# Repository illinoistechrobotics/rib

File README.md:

# Illinois Tech Robotics - Robot Interface Board (RIB)

This is a PCB design based around the existing Goliath protoboards, but adapted to work with a Raspberry Pi Pico (W), but is also usable with other robot designs using solder bridge jumpers to support various configurations. 

# Features

## Output
The majority of the circuitry allows connecting 2 OSMC's (Open Source Motor Controller) v3.22 over RJ45. They are wired with pin 2 through 9, as CAT6 only has 8 conductors and pin 1 and 10 are the same as 2 and 9 respectively, in this case we don't need the increased current offered by the extra pins.

The 10 connections for the OSMCs are just PWM or digital outputs using MCT9001 Optocouplers, by default set up for 12V (Or whatever is supplied to VIN), but with a jumper it can be set to 5V or 3.3V logic to interface with a variety of motor controllers.

There is a MAX6959 36-channel LED driver chip, that independently controls the 2-digit 7-segment display, the status LEDs of the ethernet ports, and the 3 RGB LEDs present.

## Input
2 rotary quadrature encoders can be connected with RJ45, intended to be used with the Pico's PIO. The RJ45 connections for the encoders have breakouts for Z inputs (for absolute positioning) or 2 more encoders with relative positioning only. These inputs are not connected to the Pico by default due to the limited number of GPIO pins.

There is a MCP3008 ADC which is used for battery voltage & current monitoring.

## I/O

There are 2 PCF8574 I/O expanders which are mostly ununsed, allowing for the connection of low bandwith devices (e.g. enable pins, end stops / limit switches, basic on/off logic) as their speed is limited by the I2C bus. That said, the interrupt pins are broken out and can be optionally used for a decent connection for a rotary encoder.

The first I/O expander is connected to 2 N-channel MOSFETs that are connected to the board's input voltage for VIN @ 2A (total) controllable high-power output.

There are 3 extra GPIO pins exposed, which can be used for connecting e.g. the extra encoder pins, the I/O expander interrupts, or I2C communication to other RIB(s) in order to create a megaRIB for connecting more than 2 OSMCs.

Finally, there is a place for a Digi xBee to sit and communicate with the robot over 2.4Ghz / 900 MHz radio.

## POWER 

Additionally, the PCB pulls power in from the OSMCs over the RJ45 connections or the top left terminal block. The RIB can take in from 8 to 60V of power, or you can provide 5V via headers directly. If it's necessary, the RIB can be powered by a 2S Lithium battery, the power supply can still function at around 7V in.

The onboard 5V switching power supply can provide ~1.8A and the 3v3 regulator, which pulls from the 5V line, can use up to the same 1.8A limit. The 3v3 regulator exists to  provide extra power to the xBee and 3v3 logic without having to put strain on the Pico.

The power inputs on the OSMC RJ45's can also be changed to *output* power and will match the logic voltage 5V/3.3V.

# Programming

The Pi Pico W can be programming with [Arduino-Pico](https://arduino-pico.readthedocs.io/en/latest/), the Pico C++ SDK, Micro/CircuitPython, or Embassy Rust framework. Code examples below are written based on the Arduino-Pico framework. *Note: we discovered a bug in Arduino-Pico's setXX functions affecting the RIB that is only fixed in v3.6.0 or higher.*

Things to know for programming the hardware on the RIB:

The xBee is connected to UART0 / Serial1 on the Pico via pins 16 & 17 for TX & RX respectively. 

	Serial1.setRX(17);
  	Serial1.setTX(16);

The I2C bus for the LED driver and I/O expanders is connected to I2C1 / Wire, pins 20 & 21 for SDA and SCL respectively. 

    Wire.setSDA(20);
    Wire.setSCL(21);

The LED driver has address 0x38. There is no library for the MAX6959 available online, we wrote one in [rib-test-code](https://git.myitr.org/adeck/rib-test-code). Look for lines like `Wire.beginTransmission(0x38)` and functions like `set_digit()` for example.

The I/O expanders have addresses 0x20 for the top one (connected to MOSFETs) and 0x21 for the bottom one.

The library `xreef/PCF8574` has the ability to set pins as well, so the code you would use is

    PCF8574 ioex1(0x20, 20, 21);
    PCF8574 ioex2(0x21, 20, 21);

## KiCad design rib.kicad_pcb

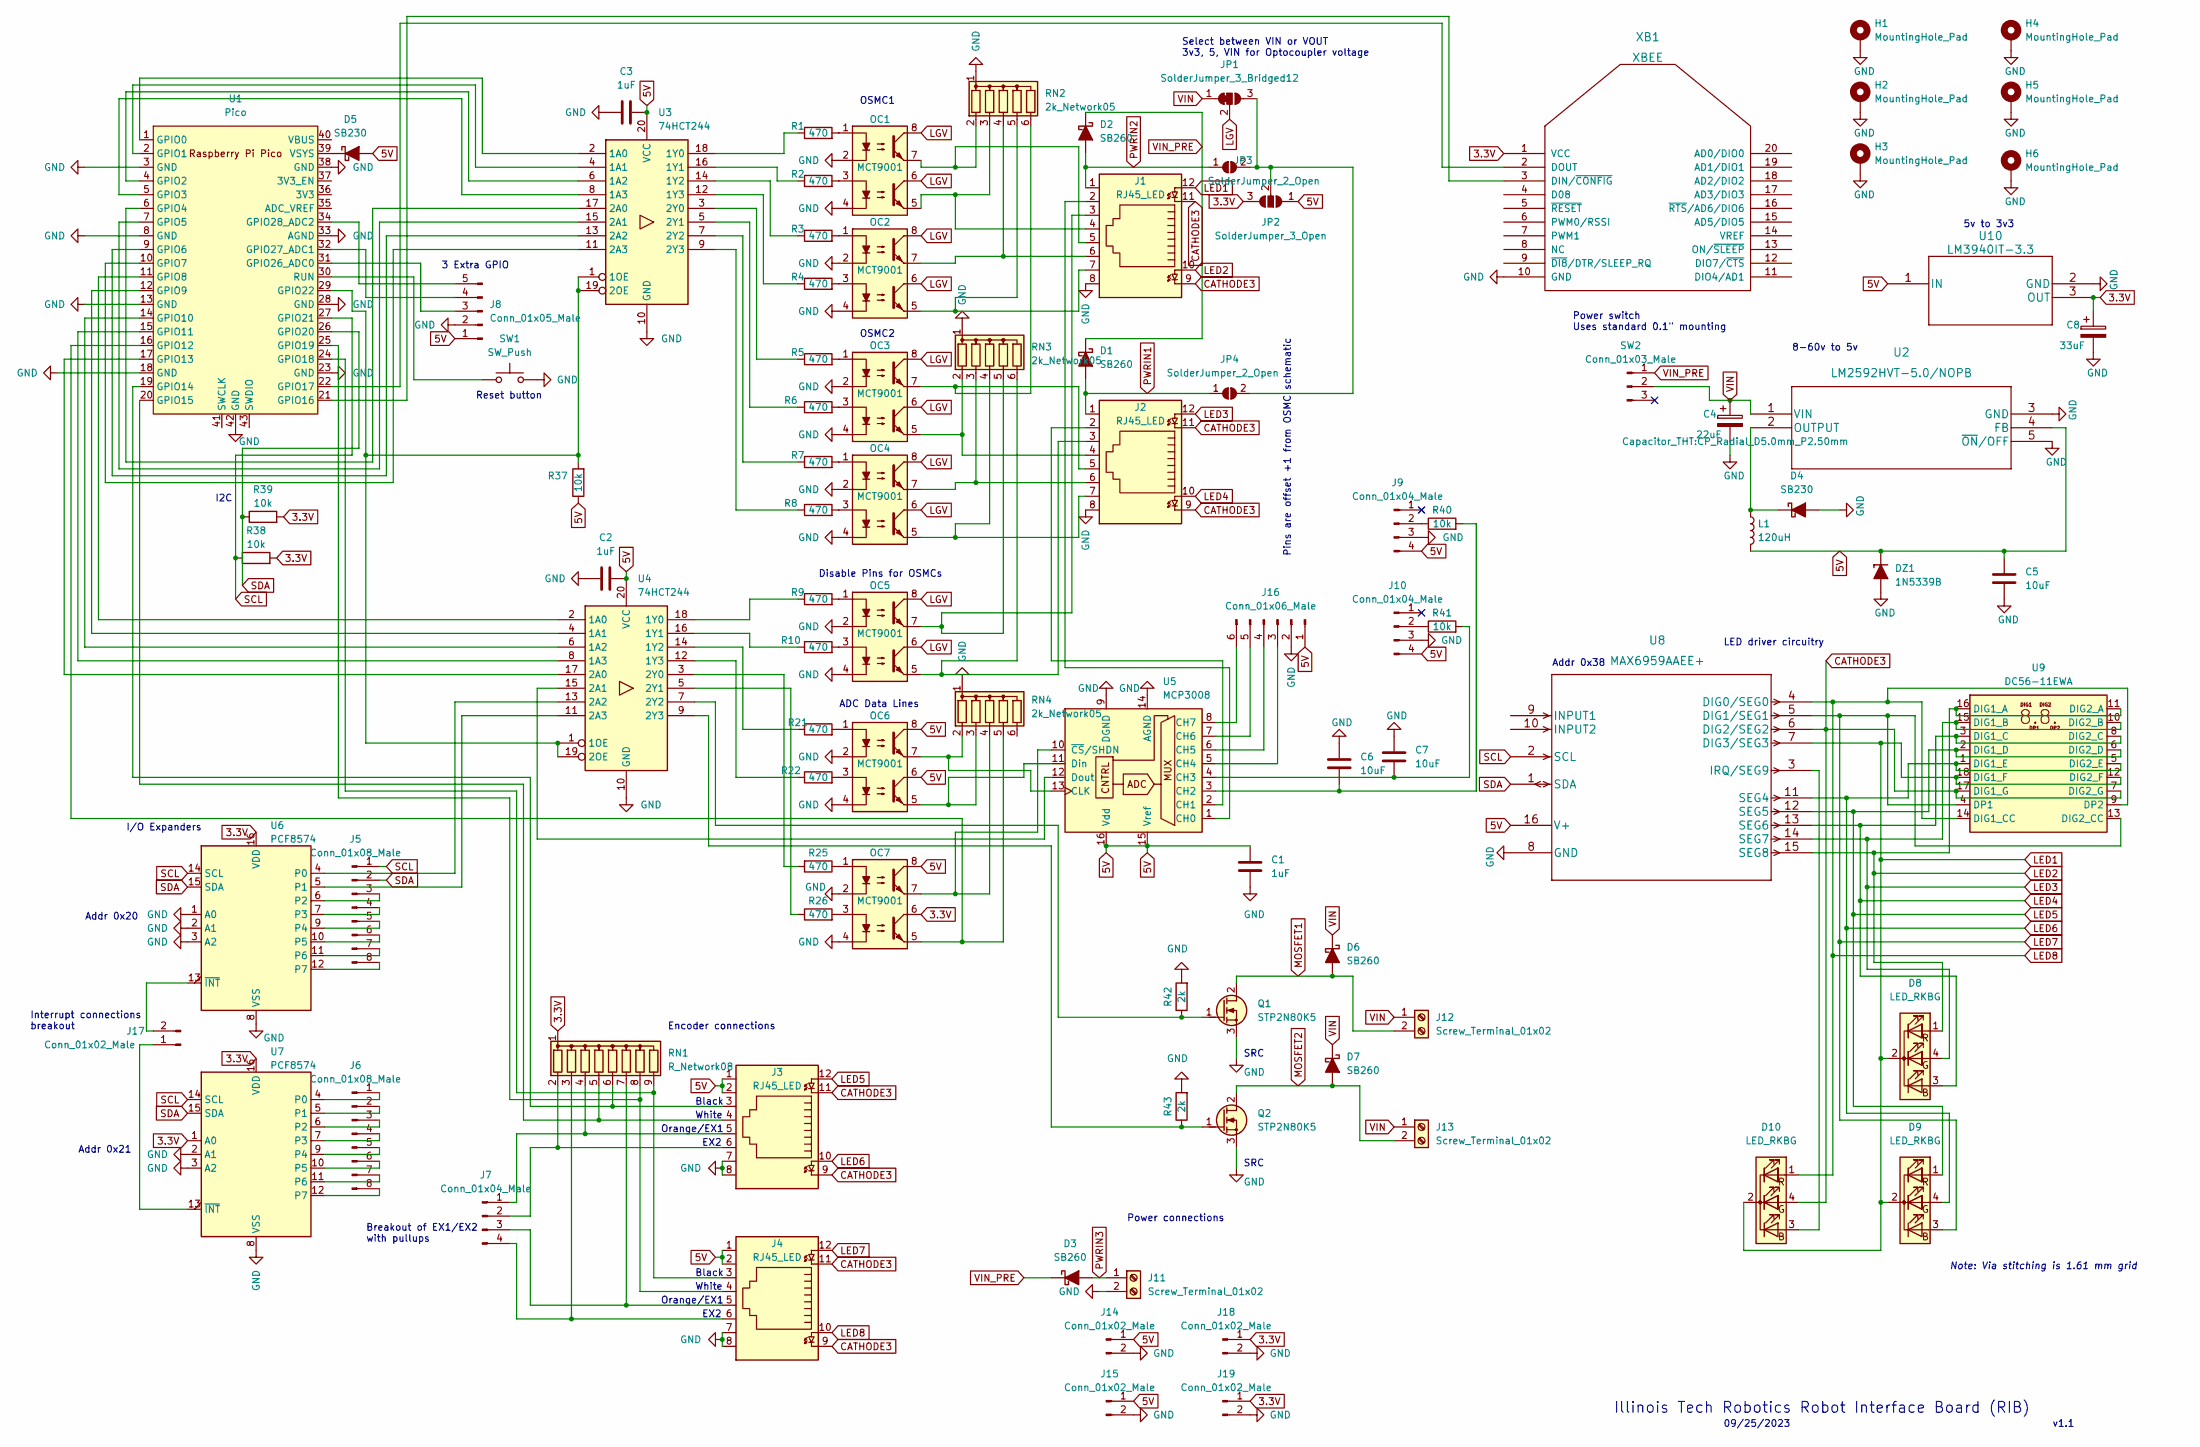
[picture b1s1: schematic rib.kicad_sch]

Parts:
C1, C2, C3: 1uF; C_Rect_L7.0mm_W4.5mm_P5.00mm
C4: 22uF; CP_Radial_D5.0mm_P2.50mm
C5, C6, C7: 10uF; C_Rect_L7.0mm_W4.5mm_P5.00mm
C8: 33uF; CP_Radial_D5.0mm_P2.50mm
D1, D2, D3, D6, D7: SB260; D_DO-15_P10.16mm_Horizontal
D4, D5: SB230; D_DO-15_P10.16mm_Horizontal
D8, D9, D10: LED_RKBG; LED_D5.0mm-4_RGB_Staggered_Pins
DZ1: 1N5339B; D_5W_CASE-017AA_P12.70mm_Horizontal_Zener
H1, H2, H3, H4, H5, H6: MountingHole_Pad; MountingHole_4.3mm_M4_Pad_Via
J1, J2, J3, J4: RJ45_LED; RJ45_Amphenol_RJHSE538X
J5, J6: Conn_01x08_Male; PinHeader_1x08_P2.54mm_Vertical
J7, J9, J10: Conn_01x04_Male; PinHeader_1x04_P2.54mm_Vertical
J8: Conn_01x05_Male; PinHeader_1x05_P2.54mm_Vertical
J11, J12, J13: Screw_Terminal_01x02; TerminalBlock_Phoenix_MKDS-1,5-2_1x02_P5.00mm_Horizontal
J14, J15, J17, J18, J19: Conn_01x02_Male; PinHeader_1x02_P2.54mm_Vertical
J16: Conn_01x06_Male; PinHeader_1x06_P2.54mm_Vertical
JP1: SolderJumper_3_Bridged12; SolderJumper-3_P1.3mm_Open_Pad1.0x1.5mm
JP2: SolderJumper_3_Open; SolderJumper-3_P1.3mm_Open_Pad1.0x1.5mm
JP3, JP4: SolderJumper_2_Open; SolderJumper-2_P1.3mm_Open_Pad1.0x1.5mm
L1: 120uH; L_Radial_D12.5mm_P7.00mm_Fastron_09HCP
OC1, OC2, OC3, OC4, OC5, OC6, OC7: MCT9001; DIP-8_W7.62mm_Socket
Q1, Q2: STP2N80K5; TO-220-3_Vertical_GDS
R1, R2, R3, R4, R5, R6, R7, R8, R9, R10, R21, R22, R25, R26: 470; R_Axial_DIN0207_L6.3mm_D2.5mm_P10.16mm_Horizontal
R37, R38, R39, R40, R41: 10k; R_Axial_DIN0207_L6.3mm_D2.5mm_P10.16mm_Horizontal
R42, R43: 2k; R_Axial_DIN0207_L6.3mm_D2.5mm_P10.16mm_Horizontal
RN1: R_Network08; R_Array_SIP9
RN2, RN3, RN4: 2k_Network05; R_Array_SIP6
SW1: SW_Push; SW_Tactile_PUSH_4.5mm_H3.8mm_TS_C016
SW2: Conn_01x03_Male; PinSocket_1x03_P2.54mm_Vertical
U1: Pico; RPi_Pico_SMD_TH
U2: LM2592HVT-5.0/NOPB; LM2592HVT-5.0&slash_NOPB
U3, U4: 74HCT244; DIP-20_W7.62mm_Socket
U5: MCP3008; DIP-16_W7.62mm_Socket
U6, U7: PCF8574; DIP-16_W7.62mm_Socket
U8: MAX6959AAEE+; DIP-16_W7.62mm_Socket
U9: DC56-11EWA; DA56-11SURKWA
U10: LM3940IT-3.3; TO-220-3_Vertical
XB1: XBEE; XBEE_PRO_PTH

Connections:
3.3V: C8.1, J18.1, J19.1, JP2.3 (B), OC7.6, R38.2, R39.2, RN1.1 (common), U6.16 (VDD), U7.1 (A0), U7.16 (VDD), U10.3 (OUT), XB1.1 (VCC)
5V: C1.1, C2.2, C3.2, C5.1, D5.2 (A), DZ1.1 (K), J3.1, J3.2, J4.1, J4.2, J8.1, J9.4, J10.4, J14.1, J15.1, J16.1, JP2.1 (A), L1.2, OC6.6, OC6.8, OC7.8, R37.1, U2.4 (FB), U3.20 (VCC), U4.20 (VCC), U5.15 (Vref), U5.16 (Vdd), U8.16 (V+), U10.1 (IN)
CATHODE3: D10.4 (GA), J1.9, J1.11, J2.9, J2.11, J3.9, J3.11, J4.9, J4.11, U8.6 (DIG2/SEG2), U9.7 (DIG2_G), U9.17 (DIG1_G)
GND: C1.2, C2.1, C3.1, C4.2, C5.2, C6.1, C7.1, C8.2, D4.2 (A), DZ1.2 (A), H1.1, H2.1, H3.1, H4.1, H5.1, H6.1, J1.8, J2.8, J3.7, J3.8, J4.7, J4.8, J8.2, J9.3, J10.3, J11.2, J14.2, J15.2, J16.2, J18.2, J19.2, OC1.2, OC1.4, OC2.2, OC2.4, OC3.2, OC3.4, OC4.2, OC4.4, OC5.2, OC5.4, OC6.2, OC6.4, OC7.2, OC7.4, Q1.3 (S), Q2.3 (S), R42.2, R43.2, RN2.1 (common), RN3.1 (common), RN4.1 (common), SW1.2, U1.3 (GND), U1.8 (GND), U1.13 (GND), U1.18 (GND), U1.23 (GND), U1.28 (GND), U1.33 (AGND), U1.38 (GND), U1.42 (GND), U2.3 (GND), U2.5 (~ON/OFF), U3.10 (GND), U4.10 (GND), U5.9 (DGND), U5.14 (AGND), U6.1 (A0), U6.2 (A1), U6.3 (A2), U6.8 (VSS), U7.2 (A1), U7.3 (A2), U7.8 (VSS), U8.8 (GND), U10.2 (GND), XB1.10 (GND)
LED1: D8.2 (K), D9.2 (K), D10.2 (K), J1.12, U8.7 (DIG3/SEG3), U9.12 (DIG2_F), U9.18 (DIG1_F)
LED2: D8.1 (RA), J1.10, U8.15 (SEG8), U9.11 (DIG2_A), U9.16 (DIG1_A)
LED3: D8.4 (GA), J2.12, U8.14 (SEG7), U9.10 (DIG2_B), U9.15 (DIG1_B)
LED4: D8.3 (BA), J2.10, U8.13 (SEG6), U9.3 (DIG1_C), U9.8 (DIG2_C)
LED5: D9.1 (RA), J3.12, U8.12 (SEG5), U9.2 (DIG1_D), U9.6 (DIG2_D)
LED6: D9.4 (GA), J3.10, U8.11 (SEG4), U9.1 (DIG1_E), U9.5 (DIG2_E)
LED7: D9.3 (BA), J4.12, U8.5 (DIG1/SEG1), U9.4 (DP1), U9.13 (DIG2_CC)
LED8: D10.1 (RA), J4.10, U8.4 (DIG0/SEG0), U9.9 (DP2), U9.14 (DIG1_CC)
LGV: JP1.2 (C), OC1.6, OC1.8, OC2.6, OC2.8, OC3.6, OC3.8, OC4.6, OC4.8, OC5.6, OC5.8
MOSFET1: D6.2 (A), J12.2, Q1.2 (D)
MOSFET2: D7.2 (A), J13.2, Q2.2 (D)
unnamed: D4.1 (K), L1.1, U2.2 (OUTPUT)
unnamed: D5.1 (K), U1.39 (VSYS)
unnamed: D10.3 (BA), U8.3 (IRQ/SEG9)
unnamed: J5.3, U6.6 (P2)
unnamed: J5.4, U6.7 (P3)
unnamed: J5.5, U6.9 (P4)
unnamed: J5.6, U6.10 (P5)
unnamed: J5.7, U6.11 (P6)
unnamed: J5.8, U6.12 (P7)
unnamed: J6.1, U7.4 (P0)
unnamed: J6.2, U7.5 (P1)
unnamed: J6.3, U7.6 (P2)
unnamed: J6.4, U7.7 (P3)
unnamed: J6.5, U7.9 (P4)
unnamed: J6.6, U7.10 (P5)
unnamed: J6.7, U7.11 (P6)
unnamed: J6.8, U7.12 (P7)
unnamed: J3.5, J7.1, RN1.4 (R3)
unnamed: J3.6, J7.2, RN1.2 (R1)
unnamed: J4.5, J7.3, RN1.7 (R6)
unnamed: J4.6, J7.4, RN1.3 (R2)
unnamed: J8.3, U1.31 (GPIO26_ADC0)
unnamed: J8.4, U1.32 (GPIO27_ADC1)
unnamed: J8.5, U1.34 (GPIO28_ADC2)
unnamed: J9.2, R40.1
unnamed: J10.2, R41.1
unnamed: J16.3, U5.5 (CH4)
unnamed: J16.4, U5.6 (CH5)
unnamed: J16.5, U5.7 (CH6)
unnamed: J16.6, U5.8 (CH7)
unnamed: J17.1, U7.13 (~INT)
unnamed: J17.2, U6.13 (~INT)
unnamed: JP1.3 (B), JP2.2 (C), JP3.2 (B), JP4.2 (B)
unnamed: OC1.1, R1.2
unnamed: OC1.3, R2.2
unnamed: OC2.1, R3.2
unnamed: OC2.3, R4.2
unnamed: OC3.1, R5.2
unnamed: OC3.3, R6.2
unnamed: OC4.1, R7.2
unnamed: OC4.3, R8.2
unnamed: OC5.1, R9.2
unnamed: OC5.3, R10.2
unnamed: OC6.1, R21.2
unnamed: OC6.3, R22.2
unnamed: OC7.1, R25.1
unnamed: OC7.3, R26.2
unnamed: Q1.1 (G), R42.1, U4.7 (2Y2)
unnamed: Q2.1 (G), R43.1, U4.9 (2Y3)
unnamed: J3.4, RN1.5 (R4), U1.20 (GPIO15)
unnamed: J3.3, RN1.6 (R5), U1.19 (GPIO14)
unnamed: J4.4, RN1.8 (R7), U1.25 (GPIO19)
unnamed: J4.3, RN1.9 (R8), U1.24 (GPIO18)
unnamed: J1.5, OC1.7, RN2.2 (R1)
unnamed: J1.4, OC1.5, RN2.3 (R2)
unnamed: J1.6, OC2.7, RN2.4 (R3)
unnamed: J1.7, OC2.5, RN2.5 (R4)
unnamed: J2.5, OC3.7, RN2.6 (R5)
unnamed: J2.4, OC3.5, RN3.2 (R1)
unnamed: J2.6, OC4.7, RN3.3 (R2)
unnamed: J2.7, OC4.5, RN3.4 (R3)
unnamed: J1.3, OC5.7, RN3.5 (R4)
unnamed: J2.3, OC5.5, RN3.6 (R5)
unnamed: OC6.7, RN4.2 (R1), U5.13 (CLK)
unnamed: OC6.5, RN4.3 (R2), U5.11 (Din)
unnamed: OC7.7, RN4.4 (R3), U5.10 (~CS/SHDN)
unnamed: OC7.5, RN4.5 (R4), U1.16 (GPIO12)
unnamed: U1.1 (GPIO0), U3.2 (1A0)
unnamed: U1.2 (GPIO1), U3.4 (1A1)
unnamed: U1.4 (GPIO2), U3.6 (1A2)
unnamed: U1.5 (GPIO3), U3.8 (1A3)
unnamed: U1.6 (GPIO4), U3.17 (2A0)
unnamed: U1.7 (GPIO5), U3.15 (2A1)
unnamed: U1.9 (GPIO6), U3.13 (2A2)
unnamed: U1.10 (GPIO7), U3.11 (2A3)
unnamed: U1.11 (GPIO8), U4.2 (1A0)
unnamed: U1.12 (GPIO9), U4.4 (1A1)
unnamed: U1.14 (GPIO10), U4.6 (1A2)
unnamed: U1.15 (GPIO11), U4.8 (1A3)
unnamed: U1.17 (GPIO13), U4.17 (2A0)
unnamed: U1.21 (GPIO16), XB1.3 (DIN/~CONFIG)
unnamed: U1.22 (GPIO17), XB1.2 (DOUT)
unnamed: R37.2, U1.29 (GPIO22), U3.1 (1OE), U3.19 (2OE), U4.1 (1OE), U4.19 (2OE)
unnamed: SW1.1, U1.30 (RUN)
unnamed: R1.1, U3.18 (1Y0)
unnamed: R2.1, U3.16 (1Y1)
unnamed: R3.1, U3.14 (1Y2)
unnamed: R4.1, U3.12 (1Y3)
unnamed: R5.1, U3.3 (2Y0)
unnamed: R6.1, U3.5 (2Y1)
unnamed: R7.1, U3.7 (2Y2)
unnamed: R8.1, U3.9 (2Y3)
unnamed: R9.1, U4.18 (1Y0)
unnamed: R10.1, U4.16 (1Y1)
unnamed: R21.1, U4.14 (1Y2)
unnamed: R22.1, U4.12 (1Y3)
unnamed: U4.15 (2A1), U5.12 (Dout)
unnamed: U4.13 (2A2), U6.4 (P0)
unnamed: U4.11 (2A3), U6.5 (P1)
unnamed: R25.2, U4.3 (2Y0)
unnamed: R26.1, U4.5 (2Y1)
unnamed: J1.2, U5.1 (CH0)
unnamed: J2.2, U5.2 (CH1)
unnamed: C6.2, R40.2, U5.3 (CH2)
unnamed: C7.2, R41.2, U5.4 (CH3)
PWRIN1: D1.2 (A), J2.1, JP4.1 (A)
PWRIN2: D2.2 (A), J1.1, JP3.1 (A)
PWRIN3: D3.2 (A), J11.1
SCL: J5.1, R38.1, U1.27 (GPIO21), U6.14 (SCL), U7.14 (SCL), U8.2 (SCL)
SDA: J5.2, R39.1, U1.26 (GPIO20), U6.15 (SDA), U7.15 (SDA), U8.1 (SDA)
VIN: C4.1, D6.1 (K), D7.1 (K), J12.1, J13.1, JP1.1 (A), SW2.2, U2.1 (VIN)
VIN_PRE: D1.1 (K), D2.1 (K), D3.1 (K), SW2.1

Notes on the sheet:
Reset button
Encoder connections
Black
I/O Expanders
Interrupt connections breakout
Power connections
5v to 3v3
3 Extra GPIO
Disable Pins for OSMCs
White
Illinois Tech Robotics Robot Interface Board (RIB)
OSMC2
OSMC1
ADC Data Lines
8-60v to 5v
Select between VIN or VOUT 3v3, 5, VIN for Optocoupler voltage
LED driver circuitry
SRC
Orange/EX1
Breakout of EX1/EX2 with pullups
09/25/2023
EX2
Note: Via stitching is 1.61 mm grid
Pins are offset +1 from OSMC schematic
Addr 0x20
Addr 0x38
I2C
Power switch Uses standard 0.1" mounting
v1.1
Addr 0x21

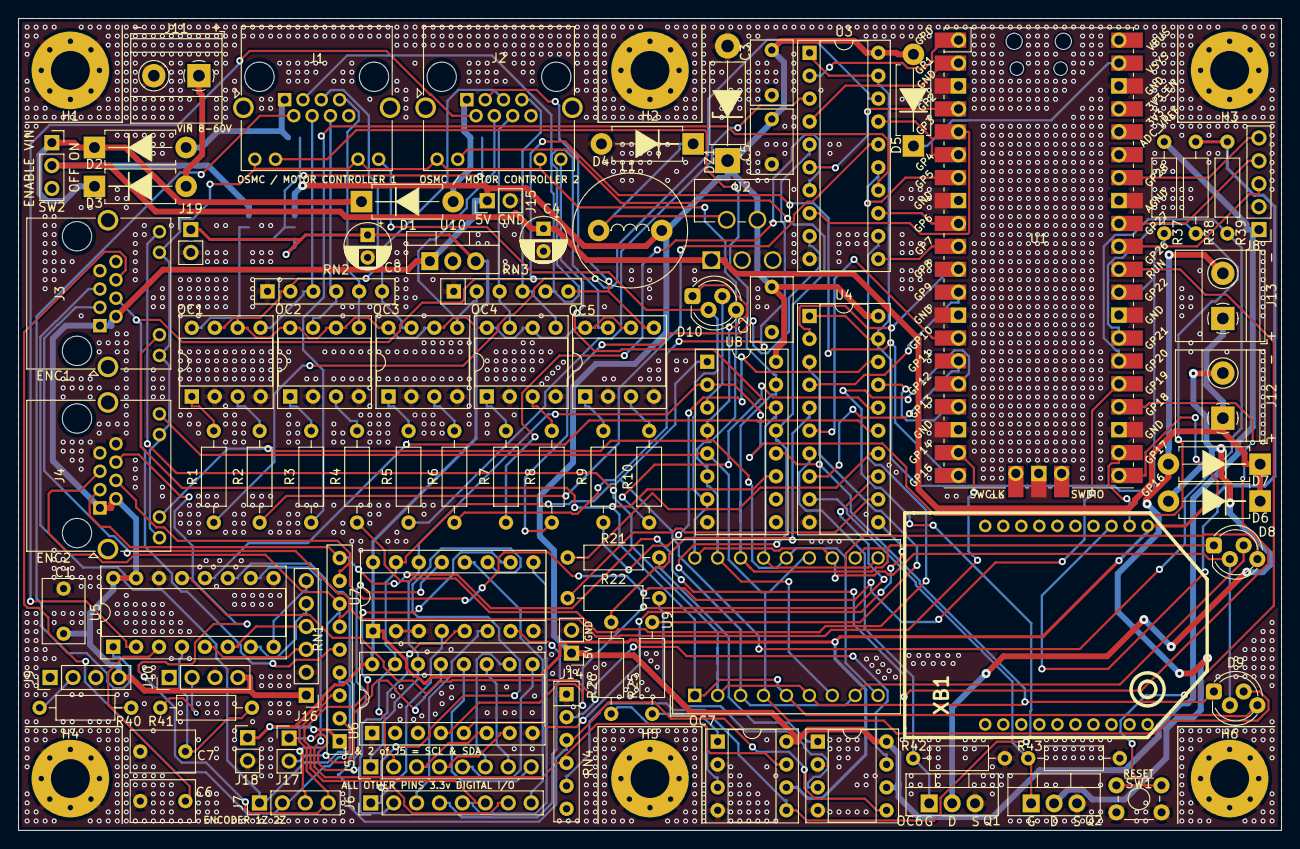
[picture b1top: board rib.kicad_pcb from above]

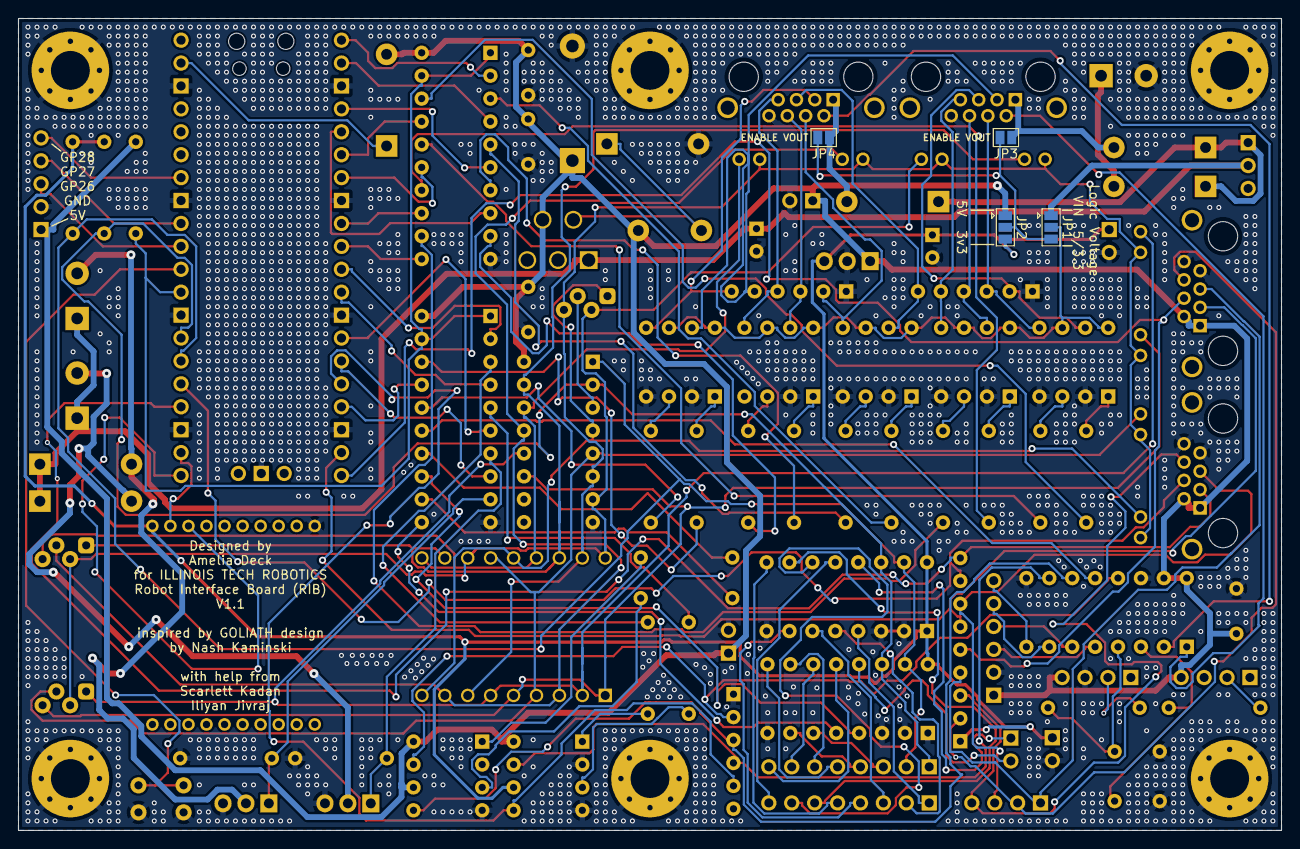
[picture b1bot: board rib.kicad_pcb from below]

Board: 2 copper layers, 140.0 x 90.0 mm, 96 parts (4 on the bottom side), 127 nets.

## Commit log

2023-02-14 Initial PCB start
2023-02-15 Add ADC for battery monitoring
2023-02-15 Add LTC1798 ADC on PCB
2023-02-15 Verify all connections, add 7805
2023-02-15 Small tweak
2023-02-15 Create todo list
2023-02-15 Move IC5 in line with other chips to avoid overlapping silkscreen
2023-02-15 Remove extra text
2023-02-15 Add buffers, restart PCB layout, start encoder stuff
2023-02-16 Layout PCB
2023-02-16 Plan for xbee support
2023-02-16 Add xBee initial plan
2023-02-20 Run traces for current version
2023-02-20 Add extra I/O and extra headers, expand PCB
2023-03-06 Add more resistors, caps
2023-03-07 Add mosfets and stuff
2023-03-07 Finish mosfet circuits, add grounding vias, mark at potential orderable prototype (add BOM)
2023-03-07 Actually connect MOSFETs to logic outputs
2023-03-08 Add comments via silkscreen, start to use alternative kicad library
2023-03-08 Add some symbol replacements
2023-03-08 Swap out all optocouplers (symbols, not the actual part)
2023-03-08 Clean up schematic
2023-03-08 Update BOM
2023-03-08 Add proper M4 mounting holes
2023-03-09 Fix silkscreen issues
2023-03-10 Prepare to swap out diodes
2023-03-10 Switch to better diodes, use via stitching plugin
2023-03-10 Adjust via stitching to alighn with silkscreen text
2023-03-10 Fix other silkscreen text
2023-03-10 Remove extra vias
2023-03-10 More via work
2023-03-10 BIG inductor
2023-03-10 Prepare RC1 for purchase
2023-03-10 Ignore output files
2023-03-10 Add a reset button, plan for power switch
2023-03-10 Add power switch, add more text, cleanup
2023-03-10 Rename project
2023-03-10 RIBodified: rib.kicad_prl
2023-03-10 Improve README
2023-03-10 Add Digi-Key parts list
2023-03-11 Oh yeah, resistor networks exist
2023-03-11 Start adding led driver
2023-03-11 Add 7seg, LED driver, connect LEDs. Fix BOM & add LEDs tomorrow
2023-03-20 Small changes
2023-03-20 Add RGB LEDs
2023-03-20 Fix keepouts for screwholes, update parts list
2023-03-20 Update CSV Digi-Key BOM
2023-03-21 Fix duplicate part
2023-03-26 Fix xbee connection visuals
2023-03-30 Fix issues with RC1 - LED orientation, pullups, 3v3 source
2023-03-30 Reroute with better trace thickness
2023-03-30 Fix track hole clearance. crashes when trying to do via stitching
2023-03-31 Make space for heatsinks
2023-03-31 Fix via stitching
2023-03-31 Update BOM (new 7seg CC, 3v3 reg LM3940, 33 uF cap), add lib
2023-03-31 Add Digi-Key BOMs for v1.0
2023-04-01 prepare to add zener diode
2023-05-18 v1.0 design update (BOMs not updated)
2023-09-28 RIB v1.1 pre-release, documentation
